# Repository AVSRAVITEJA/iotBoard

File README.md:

# iotBoard
This project showcases the complete PCB design of a custom IoT-enabled sensor board specifically developed for Unmanned Aerial Vehicles (UAVs). The board integrates several critical sensors and measurement circuits into a compact form factor, making it ideal for use in drones that require reliable and real-time data acquisition during flight. Designed with modularity, lightweight construction, and flight efficiency in mind, the board serves as a plug-and-play solution for drone developers, researchers, and enthusiasts aiming to improve onboard diagnostics and flight performance.

The sensor board includes a current sensing circuit to monitor power consumption, a voltage sensing module for battery and power system tracking, a temperature sensor to detect overheating or monitor environmental conditions, and an interface for load cells to measure payload weight or dynamic load changes during flight. These sensors provide real-time insights into the UAV's operational status, making it easier to detect anomalies, prevent system failures, and manage power resources efficiently.

This PCB is well-suited for a variety of UAV applications, such as telemetry systems, autonomous navigation, payload delivery drones, and environmental sensing platforms. By providing accurate and continuous monitoring, it enhances the reliability and intelligence of UAV systems, particularly when paired with flight controllers or IoT platforms for data logging and analysis.

Included in this repository are the complete schematic and layout files, a bill of materials (BOM) listing all components with part numbers, and Gerber files ready for PCB fabrication. Additionally, a reference designator map and basic usage documentation are provided to assist in assembly, testing, and integration.

To get started, you can manufacture the PCB using the provided Gerber files through any standard PCB fabrication service. Components listed in the BOM can be sourced from major suppliers and assembled either manually or with an SMT assembly service. Once assembled, the board can be connected to your UAV’s microcontroller or flight controller, and optionally integrated with wireless modules or IoT platforms for advanced data transmission and storage.

Future versions of this board may include features such as wireless communication (LoRa, BLE, or Wi-Fi), onboard GPS and IMU support, and compatibility with edge AI systems for real-time, autonomous decision-making. This project serves as a foundational sensor platform that can be expanded to meet the needs of various UAV missions.

| Component/Module          | Description / Value                 | Footprint / Package                        | Quantity |
| ------------------------- | ----------------------------------- | ------------------------------------------ | -------- |
| ARDUINO\_MEGA\_2560\_REV3 | Main Microcontroller Board          | ARDUINO\_ARDUINO\_MEGA\_2560\_REV3         | 1        |
| LOADCELL SECTION          | Load Cell Interface                 | RJ45\_Amphenol\_54602-x08\_Horizontal      | 1        |
| WING TILT                 | Tilt Sensor Connector               | RJ45\_Amphenol\_54602-x08\_Horizontal      | 1        |
| MOTOR currents            | Motor Current Sensor Interface      | RJ45\_Amphenol\_54602-x08\_Horizontal      | 1        |
| MOTOR TEMP                | Motor Temperature Sensor Interface  | RJ45\_Amphenol\_54602-x08\_Horizontal      | 1        |
| MOTOR RPM                 | Motor RPM Sensor Interface          | RJ45\_Amphenol\_54602-x08\_Horizontal      | 1        |
| ECU                       | ESC Connector                       | RJ45\_Amphenol\_54602-x08\_Horizontal      | 1        |
| UART                      | Serial Communication Port           | PinSocket\_2x02\_P2.54mm\_Vertical         | 1        |
| SEN-13879                 | Current Sensor Module               | SPARKFUN\_SEN-13879                        | 1        |
| MOT\_C\_GND / SIG / VCC   | Motor Current Sensor Breakout Pins  | PinHeader\_1x04\_P2.54mm                   | 3        |
| R                         | Through-Hole Resistor               | Axial\_DIN0207\_L6.3mm\_D2.5mm\_P7.62mm    | 1        |
| 113991054                 | Grove Connector Module (Likely RTC) | MODULE\_113991054                          | 1        |
| XT60PW-M                  | Power Connector (XT60)              | AMASS\_XT60PW-M\_1x02\_P7.20mm\_Horizontal | 1        |
| iot\_board                | Custom Modules (Unspecified)        | rtcModule / Untitled (Custom footprints)   | 2        |

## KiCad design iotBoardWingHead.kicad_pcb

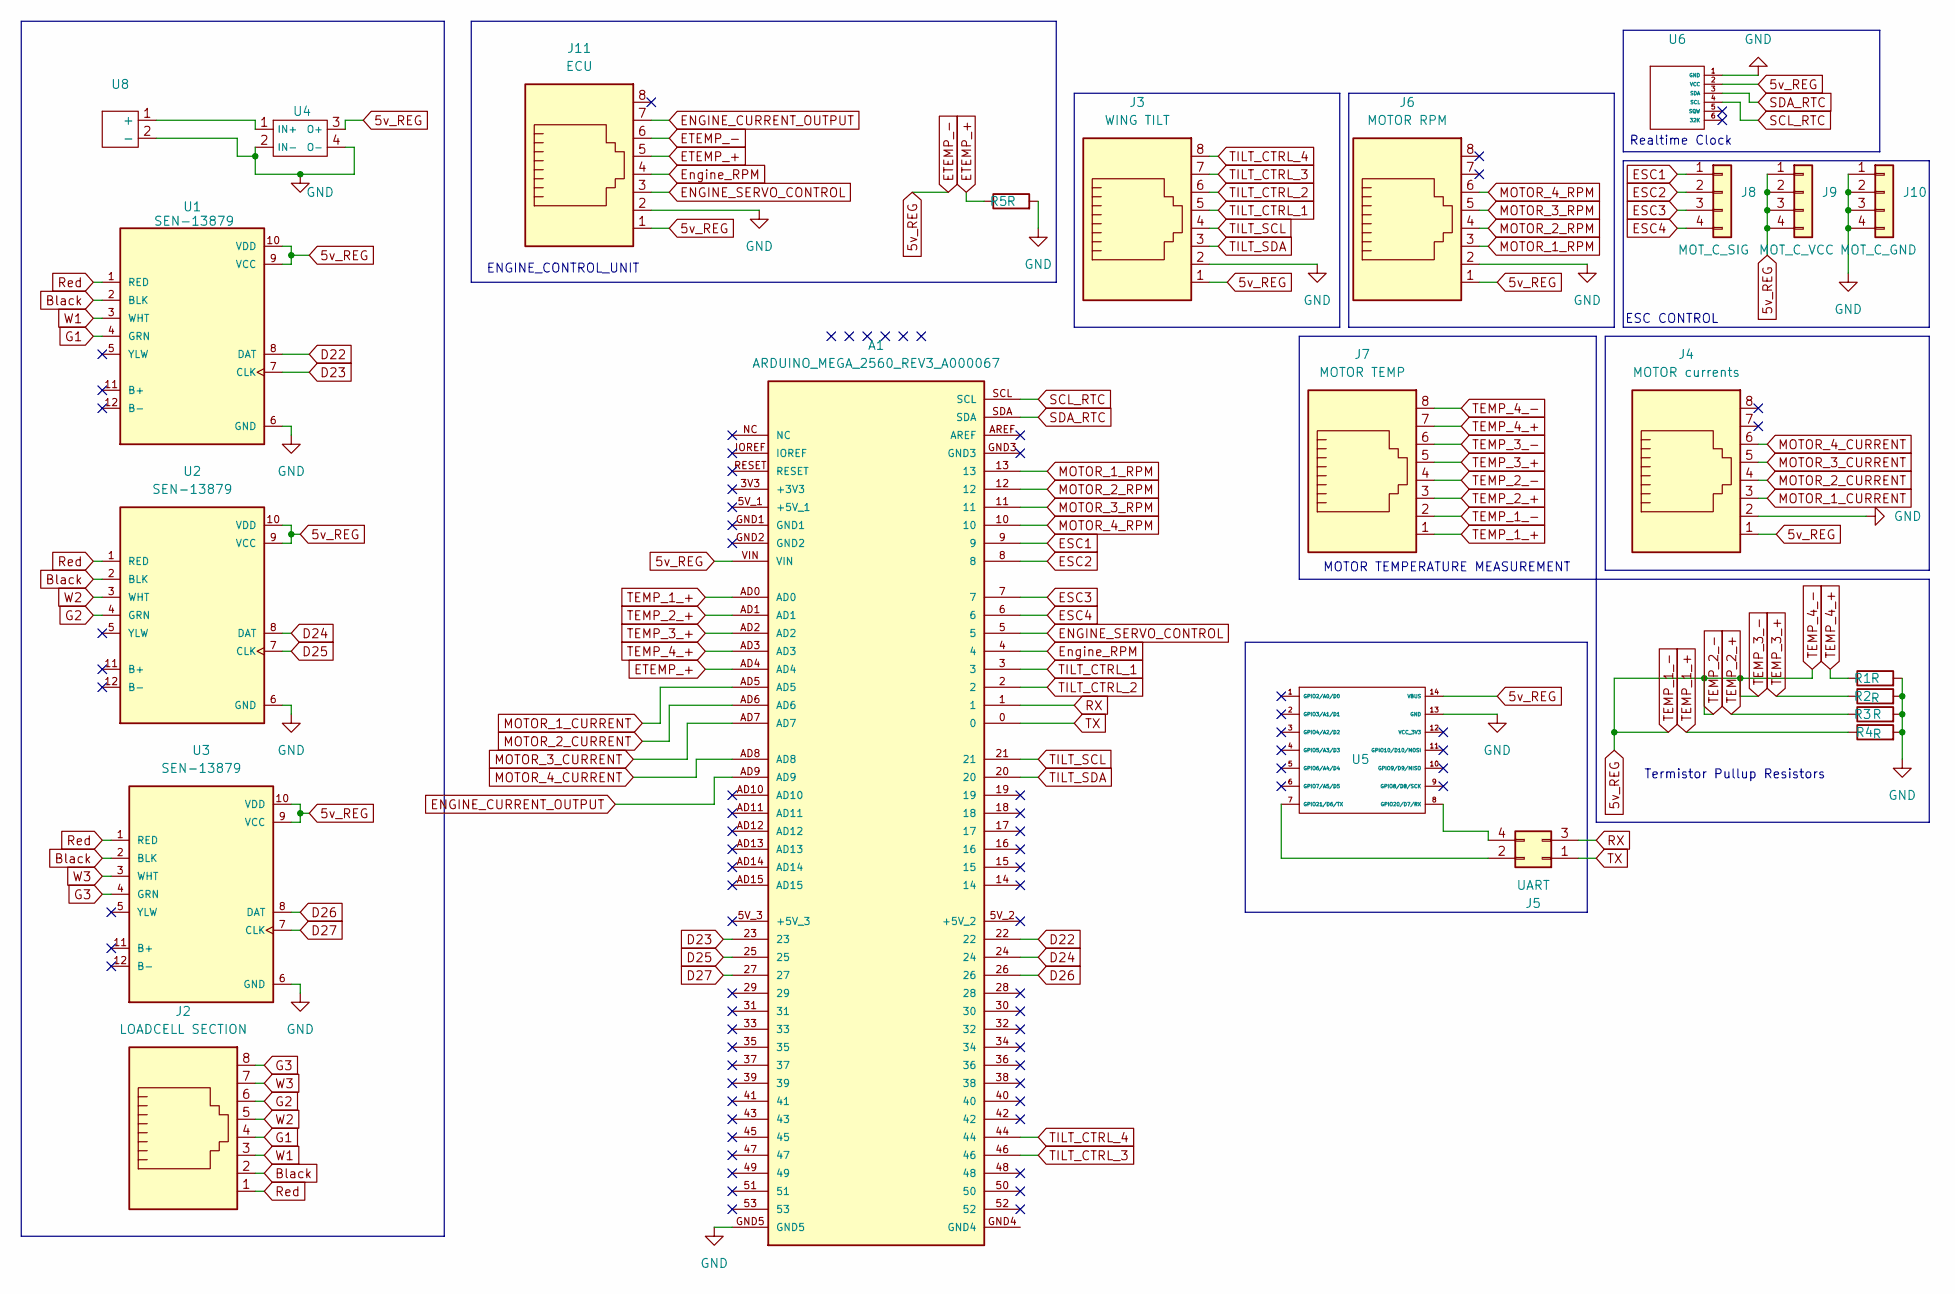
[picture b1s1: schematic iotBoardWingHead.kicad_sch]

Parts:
A1: ARDUINO_MEGA_2560_REV3_A000067; ARDUINO_ARDUINO_MEGA_2560_REV3_A000067; PARTREV 3
J2: LOADCELL SECTION; RJ45_Amphenol_54602-x08_Horizontal
J3: WING TILT; RJ45_Amphenol_54602-x08_Horizontal
J4: MOTOR currents; RJ45_Amphenol_54602-x08_Horizontal
J5: UART; PinSocket_2x02_P2.54mm_Vertical
J6: MOTOR RPM; RJ45_Amphenol_54602-x08_Horizontal
J7: MOTOR TEMP; RJ45_Amphenol_54602-x08_Horizontal
J8: MOT_C_SIG; PinHeader_1x04_P2.54mm_Vertical
J9: MOT_C_VCC; PinHeader_1x04_P2.54mm_Vertical
J10: MOT_C_GND; PinHeader_1x04_P2.54mm_Vertical
J11: ECU; RJ45_Amphenol_54602-x08_Horizontal
R1, R2, R3, R4, R5: R; R_Axial_DIN0207_L6.3mm_D2.5mm_P7.62mm_Horizontal
U1, U2, U3: SEN-13879; SPARKFUN_SEN-13879
U4: Untitled
U5: MODULE_113991054
U6: rtcModule
U8: AMASS_XT60PW-M_1x02_P7.20mm_Horizontal

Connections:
5v_REG: A1.VIN, J3.1, J4.1, J6.1, J7.2, J7.4, J7.6, J7.8, J9.1, J9.2, J9.3, J9.4, J11.1, J11.6, U1.9 (VCC), U1.10 (VDD), U2.9 (VCC), U2.10 (VDD), U3.9 (VCC), U3.10 (VDD), U4.3 (O+), U5.14 (VBUS), U6.2 (VCC)
Black: J2.2, U1.2 (BLK), U2.2 (BLK), U3.2 (BLK)
D22: A1.22, U1.8 (DAT)
D23: A1.23, U1.7 (CLK)
D24: A1.24, U2.8 (DAT)
D25: A1.25, U2.7 (CLK)
D26: A1.26, U3.8 (DAT)
D27: A1.27, U3.7 (CLK)
ENGINE_CURRENT_OUTPUT: A1.AD9, J11.7
ENGINE_SERVO_CONTROL: A1.5, J11.3
ESC1: A1.9, J8.1
ESC2: A1.8, J8.2
ESC3: A1.7, J8.3
ESC4: A1.6, J8.4
ETEMP_+: A1.AD4, J11.5, R5.1
Engine_RPM: A1.4, J11.4
G1: J2.4, U1.4 (GRN)
G2: J2.6, U2.4 (GRN)
G3: J2.8, U3.4 (GRN)
GND: A1.GND5, J3.2, J4.2, J6.2, J10.1, J10.2, J10.3, J10.4, J11.2, R1.2, R2.2, R3.2, R4.2, R5.2, U1.6 (GND), U2.6 (GND), U3.6 (GND), U4.2 (IN-), U4.4 (O-), U5.13 (GND), U6.1 (GND), U8.2 (-)
MOTOR_1_CURRENT: A1.AD5, J4.3
MOTOR_1_RPM: A1.13, J6.3
MOTOR_2_CURRENT: A1.AD6, J4.4
MOTOR_2_RPM: A1.12, J6.4
MOTOR_3_CURRENT: A1.AD7, J4.5
MOTOR_3_RPM: A1.11, J6.5
MOTOR_4_CURRENT: A1.AD8, J4.6
MOTOR_4_RPM: A1.10, J6.6
unnamed: J5.2, U5.7 (GPIO21/D6/TX)
unnamed: J5.4, U5.8 (GPIO20/D7/RX)
unnamed: U4.1 (IN+), U8.1 (+)
RX: A1.1, J5.3
Red: J2.1, U1.1 (RED), U2.1 (RED), U3.1 (RED)
SCL_RTC: A1.SCL, U6.4 (SCL)
SDA_RTC: A1.SDA, U6.3 (SDA)
TEMP_1_+: A1.AD0, J7.1, R4.1
TEMP_2_+: A1.AD1, J7.3, R3.1
TEMP_3_+: A1.AD2, J7.5, R2.1
TEMP_4_+: A1.AD3, J7.7, R1.1
TILT_CTRL_1: A1.3, J3.5
TILT_CTRL_2: A1.2, J3.6
TILT_CTRL_3: A1.46, J3.7
TILT_CTRL_4: A1.44, J3.8
TILT_SCL: A1.21, J3.4
TILT_SDA: A1.20, J3.3
TX: A1.0, J5.1
W1: J2.3, U1.3 (WHT)
W2: J2.5, U2.3 (WHT)
W3: J2.7, U3.3 (WHT)

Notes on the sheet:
Termistor Pullup Resistors
ENGINE_CONTROL_UNIT
Realtime Clock
MOTOR TEMPERATURE MEASUREMENT
ESC CONTROL

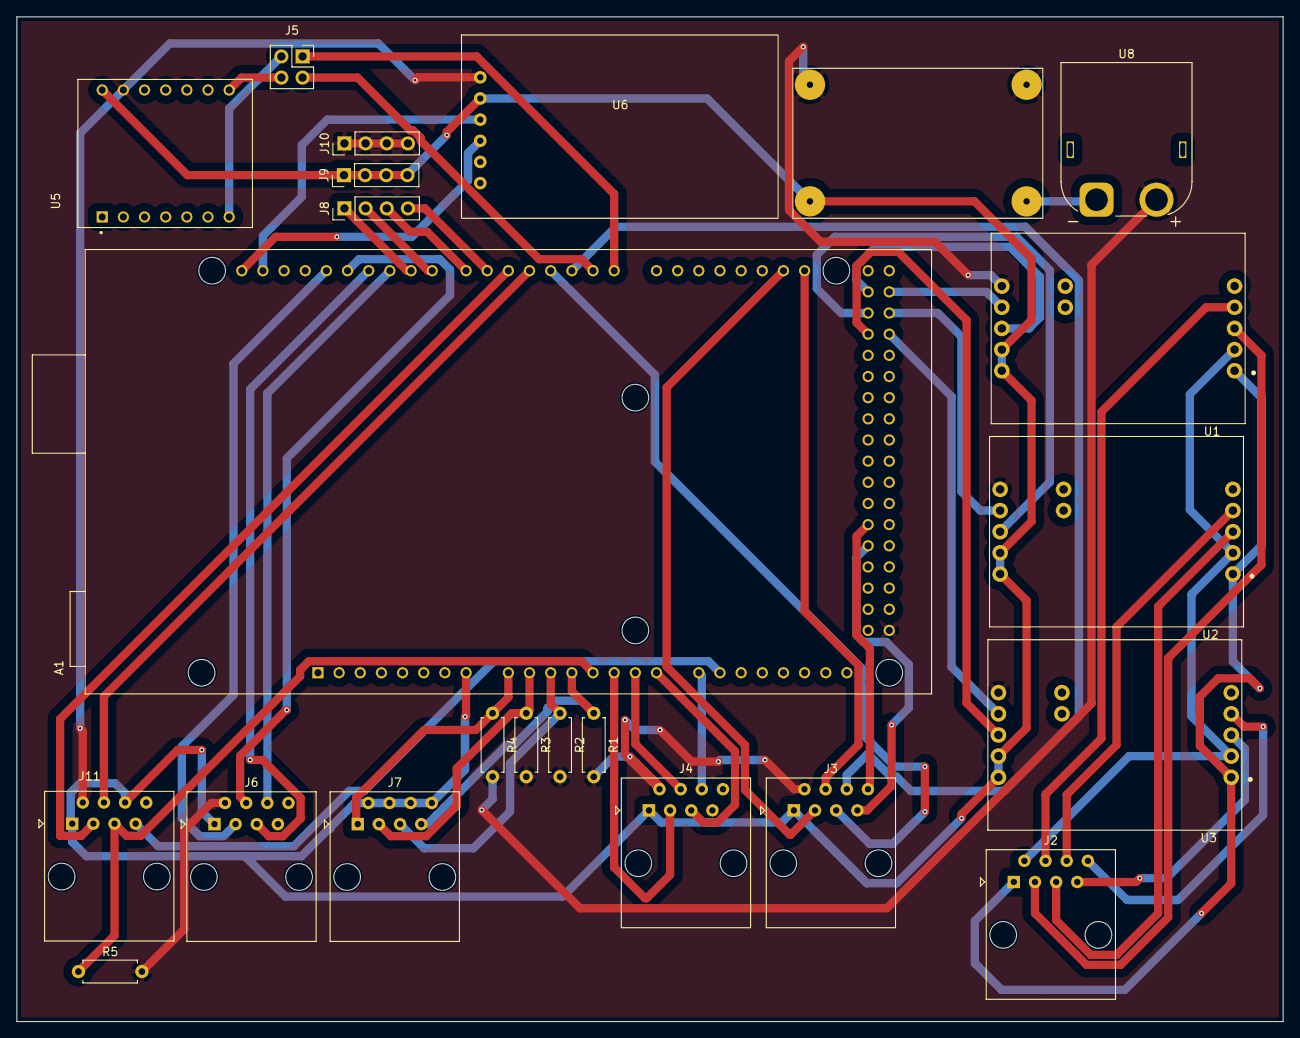
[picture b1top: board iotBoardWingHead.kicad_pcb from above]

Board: 2 copper layers, 152.0 x 120.6 mm, 23 parts (0 on the bottom side), 49 nets.
